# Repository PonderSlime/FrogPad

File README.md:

# Frogpad
This is my design for Hack Club's Hackpad Challenge. It features a rotary encoder, 15 switches, and a charming froggy face.
<details>
<summary>

# Details
</summary>
<details>

<summary>

## The PCB
</summary>
The first step in my design was to create the pcb schematic.
This involved choosing what components to use and how they should be wired to each other. Overall, this was the easiest step in the design process, since
I am only using 15 switches and 1 rotary encoder.

The next step was for me to decide on a layout for my board.
I decided to go for an erginomic key layout. The encoder sits conveniently in a spot that could be considered a "nose." The macropad truly became a frog when
I decided that I wanted a unique outline and couldn't quite achieve what I was initally going for. During the case design, I was forced to relocate the SeeedStudio
XIAO RP2040 several times, to allow it to plug in better. I also modified the through-hole sizes several times for a similar reason: I needed the case to stay together.

I made many mistakes on the way of my project, and several times had to completely rebuild my case design. Although I encountered many setbacks, 
I still continued on. The hardest thing with designing the pcb was when I was forced to completely restart on the wire traces due to a slight layout change.

</details>
<details>
<summary>

## The Case

</summary>
For this step I decided to use Onshape. Since this was my first time using Onshape, this took longer than i had hoped for. Luckily, after learning the basics, it was pretty easy to design my case to fit my board. I'm really happy with how it turned out.
</details>
<details>
<summary>

## The Firmware
</summary>
In the past, i have mainly used python for my hardware projects (the only one to date being for bin.) However, in my mind, this project is more like professional design. Since this was the case, I decided to use a dedicated keyboard firmware tool: QMK. I struggled a lot on this step, since i couldn't immediatly find a good firmware base for the RP2040. In the end, I was able to finish the firmware succesfully, with support for the encoder and all 15 keys.
</details>
<details>
<summary>

## In Retrospect
</summary>

During the time spent designing my macropad, I learned more about how to use Kicad, Onshape and QMK. All of these tools were hard in there own way.

Kicad was difficult for me due to the unique board outline and drill hole sizes.

Onshape was tricky because it was my first time using 3D cad software other than Blender.

OMK was especially difficult due to lack of information on using a RP2040 microcontroller.# PonderSime-Hackpad
</details>

</details>

# Keymaps
### Layer 0
| ______ | Space | TO(2) | ______ | ______ |
| ------ | ------ | ------  | ------| ------| 
| Q | W | E | R | T |
| A | S | D | F | G |
| Z | X | C | V | TD(0) |

### Layer 1
| ______ | Space | TO(2) | ______ | ______ |
| ------ | ------ | ------  | ------| ------| 
| Y | U | I | O | P |
| H | J | K | L | . |
| B | N | M | , |  |

### Layer 2
| ______ | TO(0) | TO(3) | ______ | ______ |
| ------ | ------ | ------  | ------| ------| 
| TD(2) | TD(3) | TD(4) | TD(5) | TD(6) |
| TD(7) | TD(8) | TD(9) | TD(10) | TD(11) |
| Left | Up | Down | Right | TD(1) |

### Layer 3
| ______ | TO(2) | Space | ______ | ______ |
| ------ | ------ | ------  | ------| ------| 
| F1 | F2 | F3 | F4 | F5 |
| F6 | F7 | F8 | F9 | F10 |
| F11 | F12 | Esc | Tab |  |

## Tap-Dance Info
| Which One | On Tap | On Hold | Double Tap | Tap and Hold |
| ------ | ------ | ------ | ------ | ------ |
| 0 | Space | MO(1) | Enter | Bksp | 
| 1 | Space | MO(3) | Enter | Bksp | 
| 2 | 1 |  | 6 |  | 
| 3 | 2 |  | 7 |  | 
| 4 | 3 |  | 8 |  | 
| 5 | 4 |  | 9 |  | 
| 6 | 5 |  | 0 |  | 
| 7 | - |  | = |  | 
| 8 | ' |  | ` |  | 
| 9 | [ |  | ] |  | 
| 10 | Esc |  | / |  | 
| 11 | \ |  | Caps |  |

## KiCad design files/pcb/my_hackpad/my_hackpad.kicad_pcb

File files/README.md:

# Frogpad

# BOM:
- 15x Cherry MX switches (through hole)
- 15x 0805 (2012 metric) 1.5x1.40mm HandSolder Diodes (whatever one has specs closest to 1n4148 diodes)
- 1x Alps Alpine EC11E Switch Encoder
- 1x PCB
- 1x SeeedStudio XIAO RP2040 microcontroller

# 3D Prints
- 1x Case Top
- 1x Case Bottom
- 1x Rotary encoder cap (scaling is wrong for some reason, i dont need a massive encoder cap!)

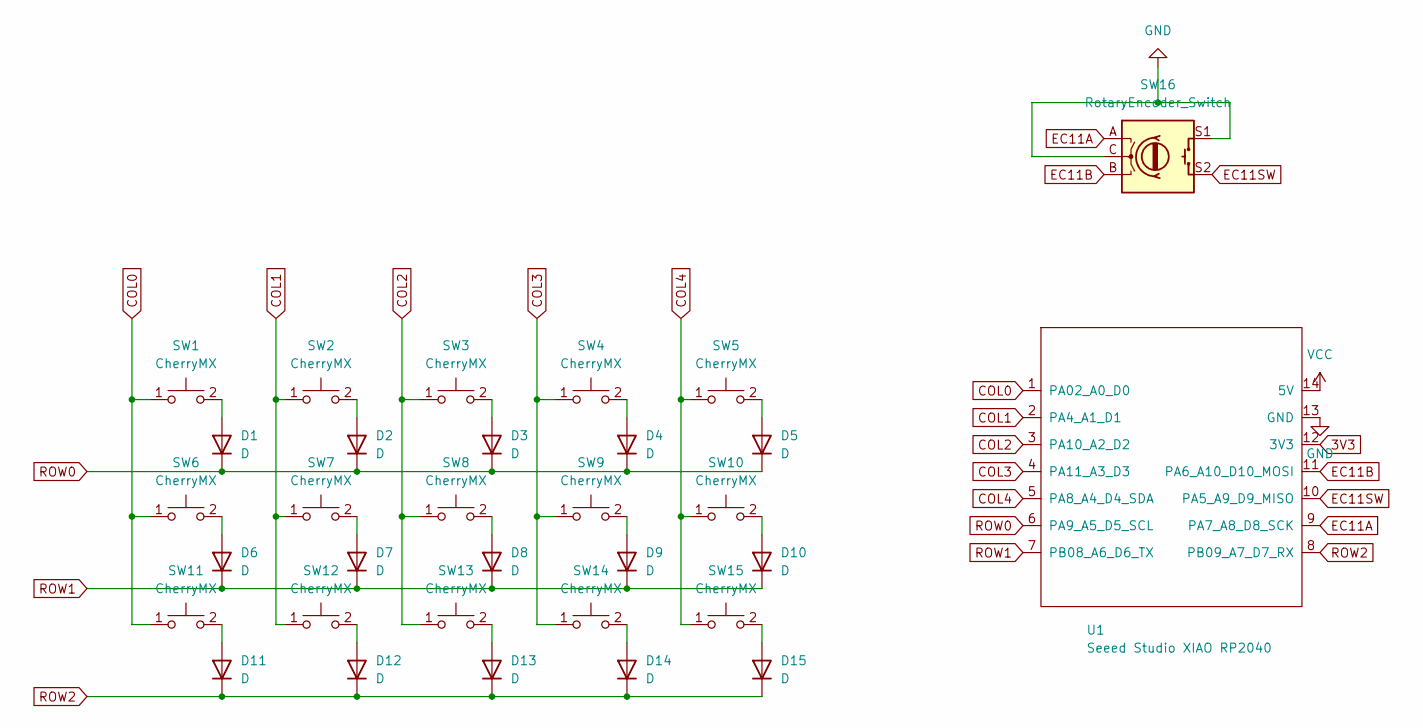
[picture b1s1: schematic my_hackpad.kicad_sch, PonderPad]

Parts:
D1, D2, D3, D4, D5, D6, D7, D8, D9, D10, D11, D12, D13, D14, D15: D; D_0805_2012Metric_Pad1.15x1.40mm_HandSolder
SW1, SW2, SW3, SW4, SW5, SW6, SW7, SW8, SW9, SW10, SW11, SW12, SW13, SW14, SW15: CherryMX; SW_Cherry_MX_PCB_1.00u
SW16: RotaryEncoder_Switch; RotaryEncoder_Alps_EC11E-Switch_Vertical_H20mm
U1: Seeed Studio XIAO RP2040; XIAO-Generic-Thruhole-14P-2.54-21X17.8MM

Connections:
3V3: U1.12 (3V3)
COL0: SW1.1, SW6.1, SW11.1, U1.1 (PA02_A0_D0)
COL1: SW2.1, SW7.1, SW12.1, U1.2 (PA4_A1_D1)
COL2: SW3.1, SW8.1, SW13.1, U1.3 (PA10_A2_D2)
COL3: SW4.1, SW9.1, SW14.1, U1.4 (PA11_A3_D3)
COL4: SW5.1, SW10.1, SW15.1, U1.5 (PA8_A4_D4_SDA)
EC11A: SW16.A, U1.9 (PA7_A8_D8_SCK)
EC11B: SW16.B, U1.11 (PA6_A10_D10_MOSI)
EC11SW: SW16.S2, U1.10 (PA5_A9_D9_MISO)
GND: SW16.C, SW16.S1, U1.13 (GND)
unnamed: D1.2 (A), SW1.2
unnamed: D2.2 (A), SW2.2
unnamed: D3.2 (A), SW3.2
unnamed: D4.2 (A), SW4.2
unnamed: D5.2 (A), SW5.2
unnamed: D6.2 (A), SW6.2
unnamed: D7.2 (A), SW7.2
unnamed: D8.2 (A), SW8.2
unnamed: D9.2 (A), SW9.2
unnamed: D10.2 (A), SW10.2
unnamed: D11.2 (A), SW11.2
unnamed: D12.2 (A), SW12.2
unnamed: D13.2 (A), SW13.2
unnamed: D14.2 (A), SW14.2
unnamed: D15.2 (A), SW15.2
ROW0: D1.1 (K), D2.1 (K), D3.1 (K), D4.1 (K), D5.1 (K), U1.6 (PA9_A5_D5_SCL)
ROW1: D6.1 (K), D7.1 (K), D8.1 (K), D9.1 (K), D10.1 (K), U1.7 (PB08_A6_D6_TX)
ROW2: D11.1 (K), D12.1 (K), D13.1 (K), D14.1 (K), D15.1 (K), U1.8 (PB09_A7_D7_RX)
VCC: U1.14 (5V)

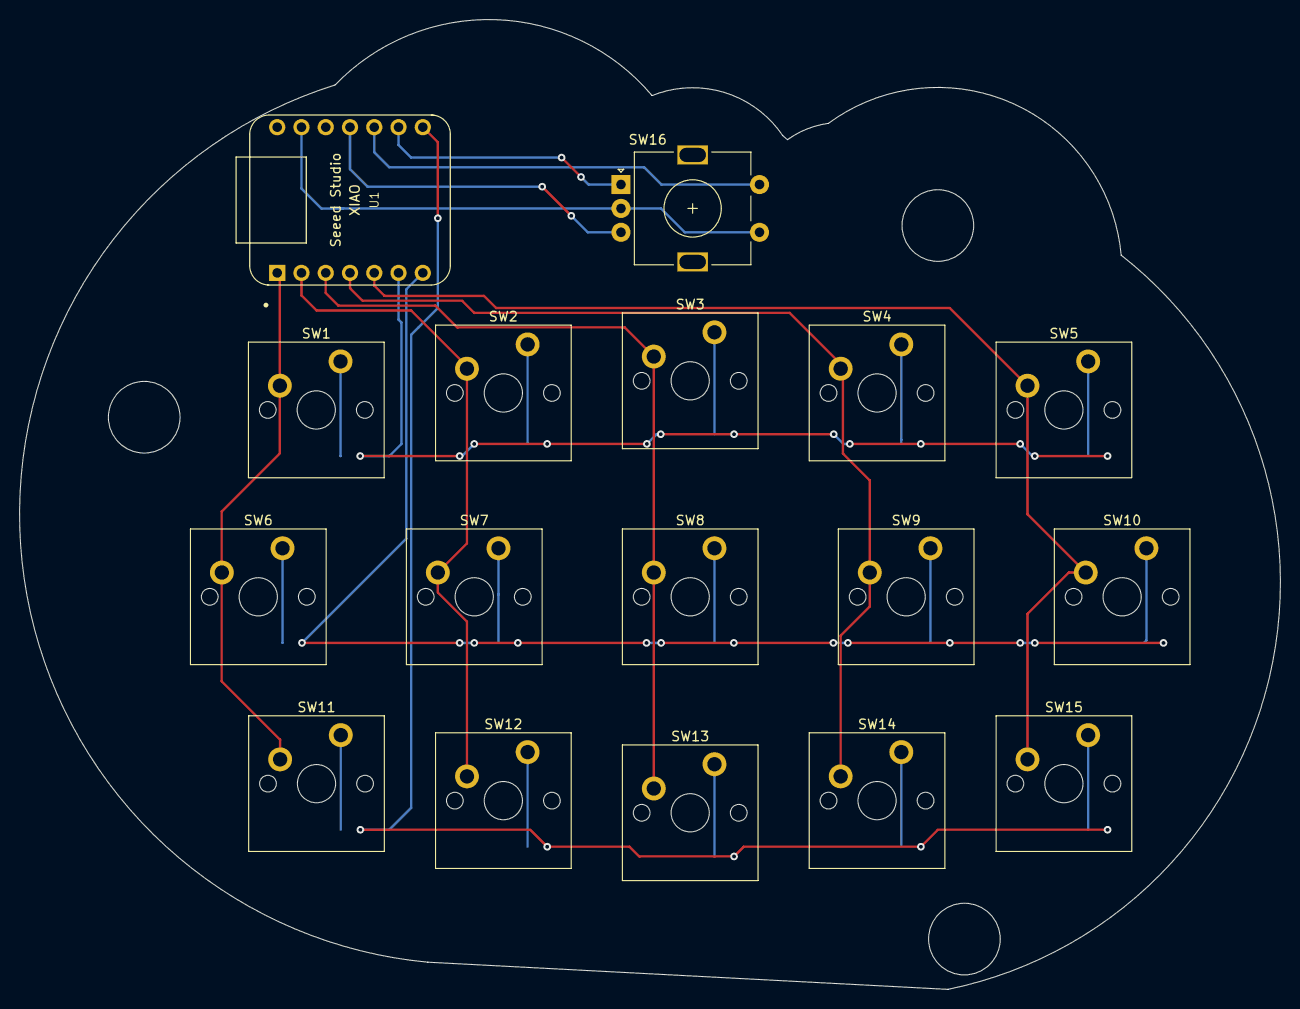
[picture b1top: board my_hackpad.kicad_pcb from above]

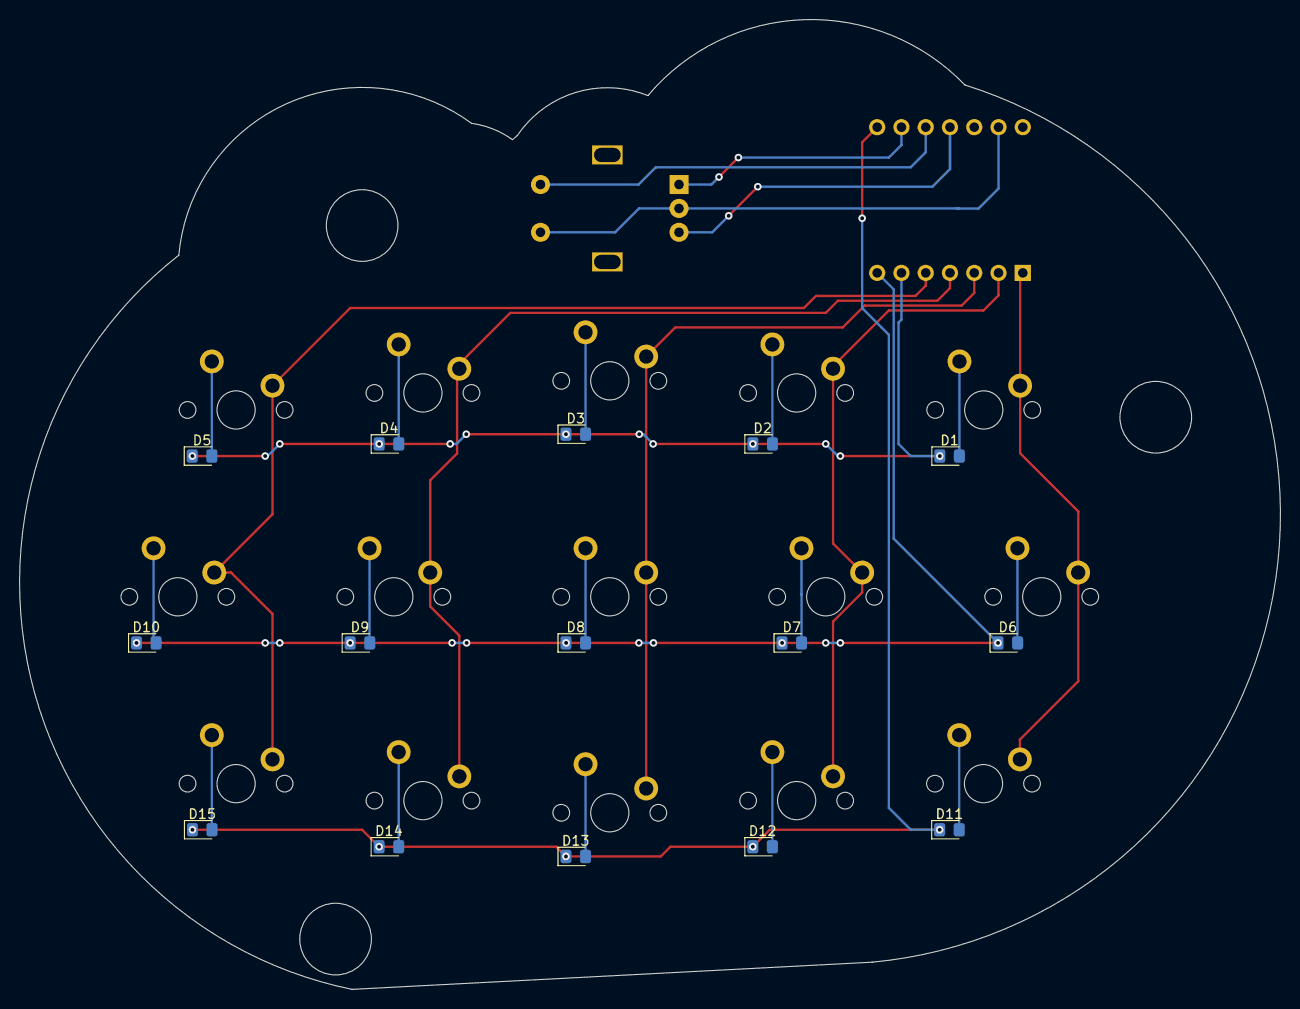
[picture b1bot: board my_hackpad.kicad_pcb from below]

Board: 2 copper layers, 132.0 x 101.5 mm, 32 parts (15 on the bottom side), 27 nets.

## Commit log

2024-09-12 KiCad Project started
2024-09-15 Libraries added, schematic done
2024-09-16 Key layout finished, wire routing started
2024-09-20 Libraries added, case design started, PCB routing complete
2024-09-23 PCB Finished
2024-09-23 more files deleted
2024-09-27 Case updated
2024-10-09 Firmware Complete
2024-10-09 Case added, GND plane fixed
2024-10-09 Actual gnd plane fixed
2024-10-10 PCB wire traces updated
2024-10-10 Through holes fixed
2024-10-10 Case updated, through holes fixed
2024-10-12 Files reorganized, backups removed
2024-10-13 gbr files added
2025-03-27 Gitignore got borked
2025-03-27 Ig i can't ignore stuff...
2025-03-27 Fixed readme stuff
2025-03-28 Layout fully ready
2025-03-28 Added chording layout and blank layout
2025-03-28 Added missing firmware stuff
2025-03-29 Firmware moved to be more json-centric
2025-04-02 Chording layout fixed
